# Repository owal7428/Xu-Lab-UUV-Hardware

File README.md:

# Xu-Lab-UUV-Hardware
Hardware design for Xu Lab underwater modular robotic platform project.

Controller board: <br>

Power board: <br>

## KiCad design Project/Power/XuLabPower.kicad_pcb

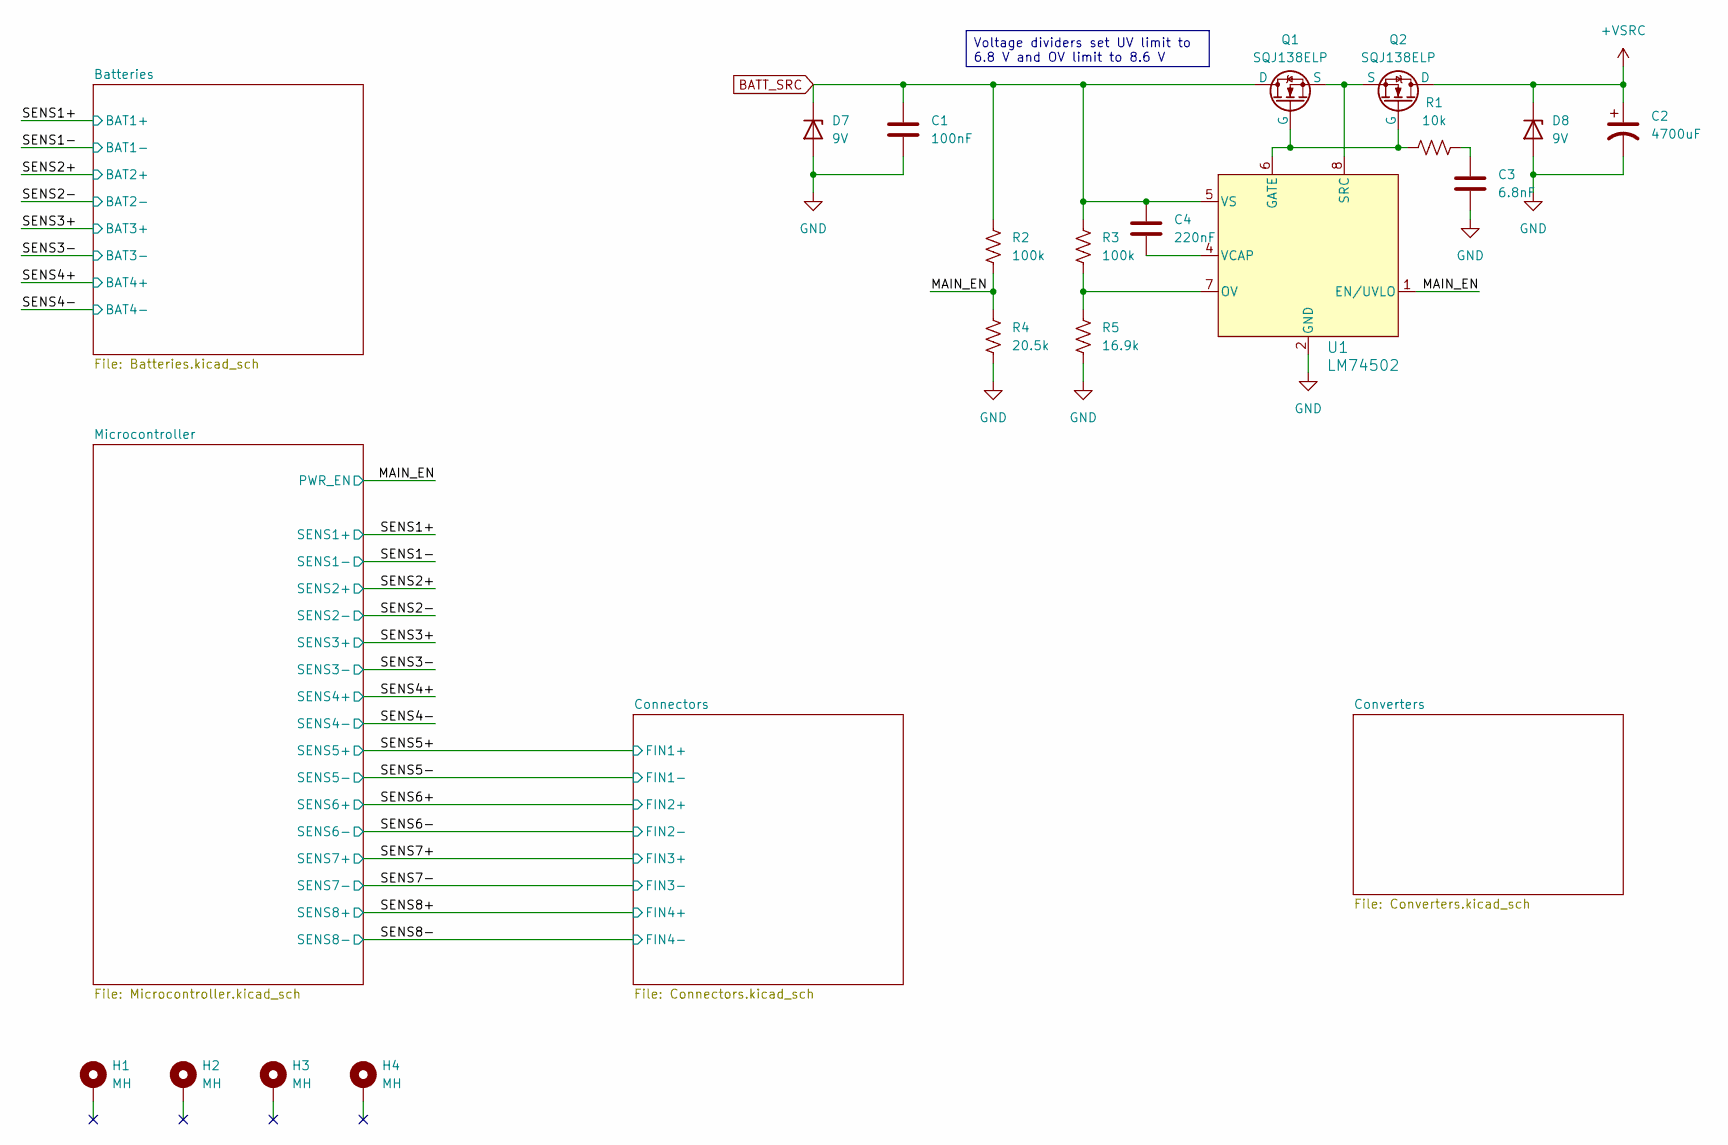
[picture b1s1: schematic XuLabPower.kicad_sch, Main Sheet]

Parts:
C1: 100nF; C_0603_1608Metric
C2: 4700uF; CP_Radial_D12.5mm_P5.00mm
C3: 6.8nF; C_0603_1608Metric
C4: 220nF; C_0603_1608Metric
D7, D8: 9V; D_SMB
H1, H2, H3, H4: MH; MountingHole_2.7mm_M2.5_Pad_Via
Q1, Q2: SQJ138ELP; PowerPAK_SO-8L
R1: 10k; R_0603_1608Metric
R2, R3: 100k; R_0603_1608Metric
R4: 20.5k; R_0603_1608Metric
R5: 16.9k; R_0603_1608Metric
U1: LM74502; TSOT-23-8

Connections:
+VSRC: C2.1, D8.1 (K), Q2.5 (D); also elsewhere on the board
/MAIN_EN: R2.2, R4.1, U1.1 (EN/UVLO); also elsewhere on the board
BATT_SRC: C1.1, C4.1, D7.1 (K), Q1.5 (D), R2.1, R3.1, U1.5 (VS); also elsewhere on the board
GND: C1.2, C2.2, C3.2, D7.2 (A), D8.2 (A), R4.2, R5.2, U1.2 (GND); also elsewhere on the board
unnamed: C3.1, R1.2
unnamed: Q1.4 (G), Q2.4 (G), R1.1, U1.6 (GATE)
unnamed: R3.2, R5.1, U1.7 (OV)
unnamed: Q1.1 (S), Q1.2 (S), Q1.3 (S), Q2.1 (S), Q2.2 (S), Q2.3 (S), U1.8 (SRC)
unnamed: C4.2, U1.4 (VCAP)

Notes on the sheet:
Voltage dividers set UV limit to 6.8 V and OV limit to 8.6 V

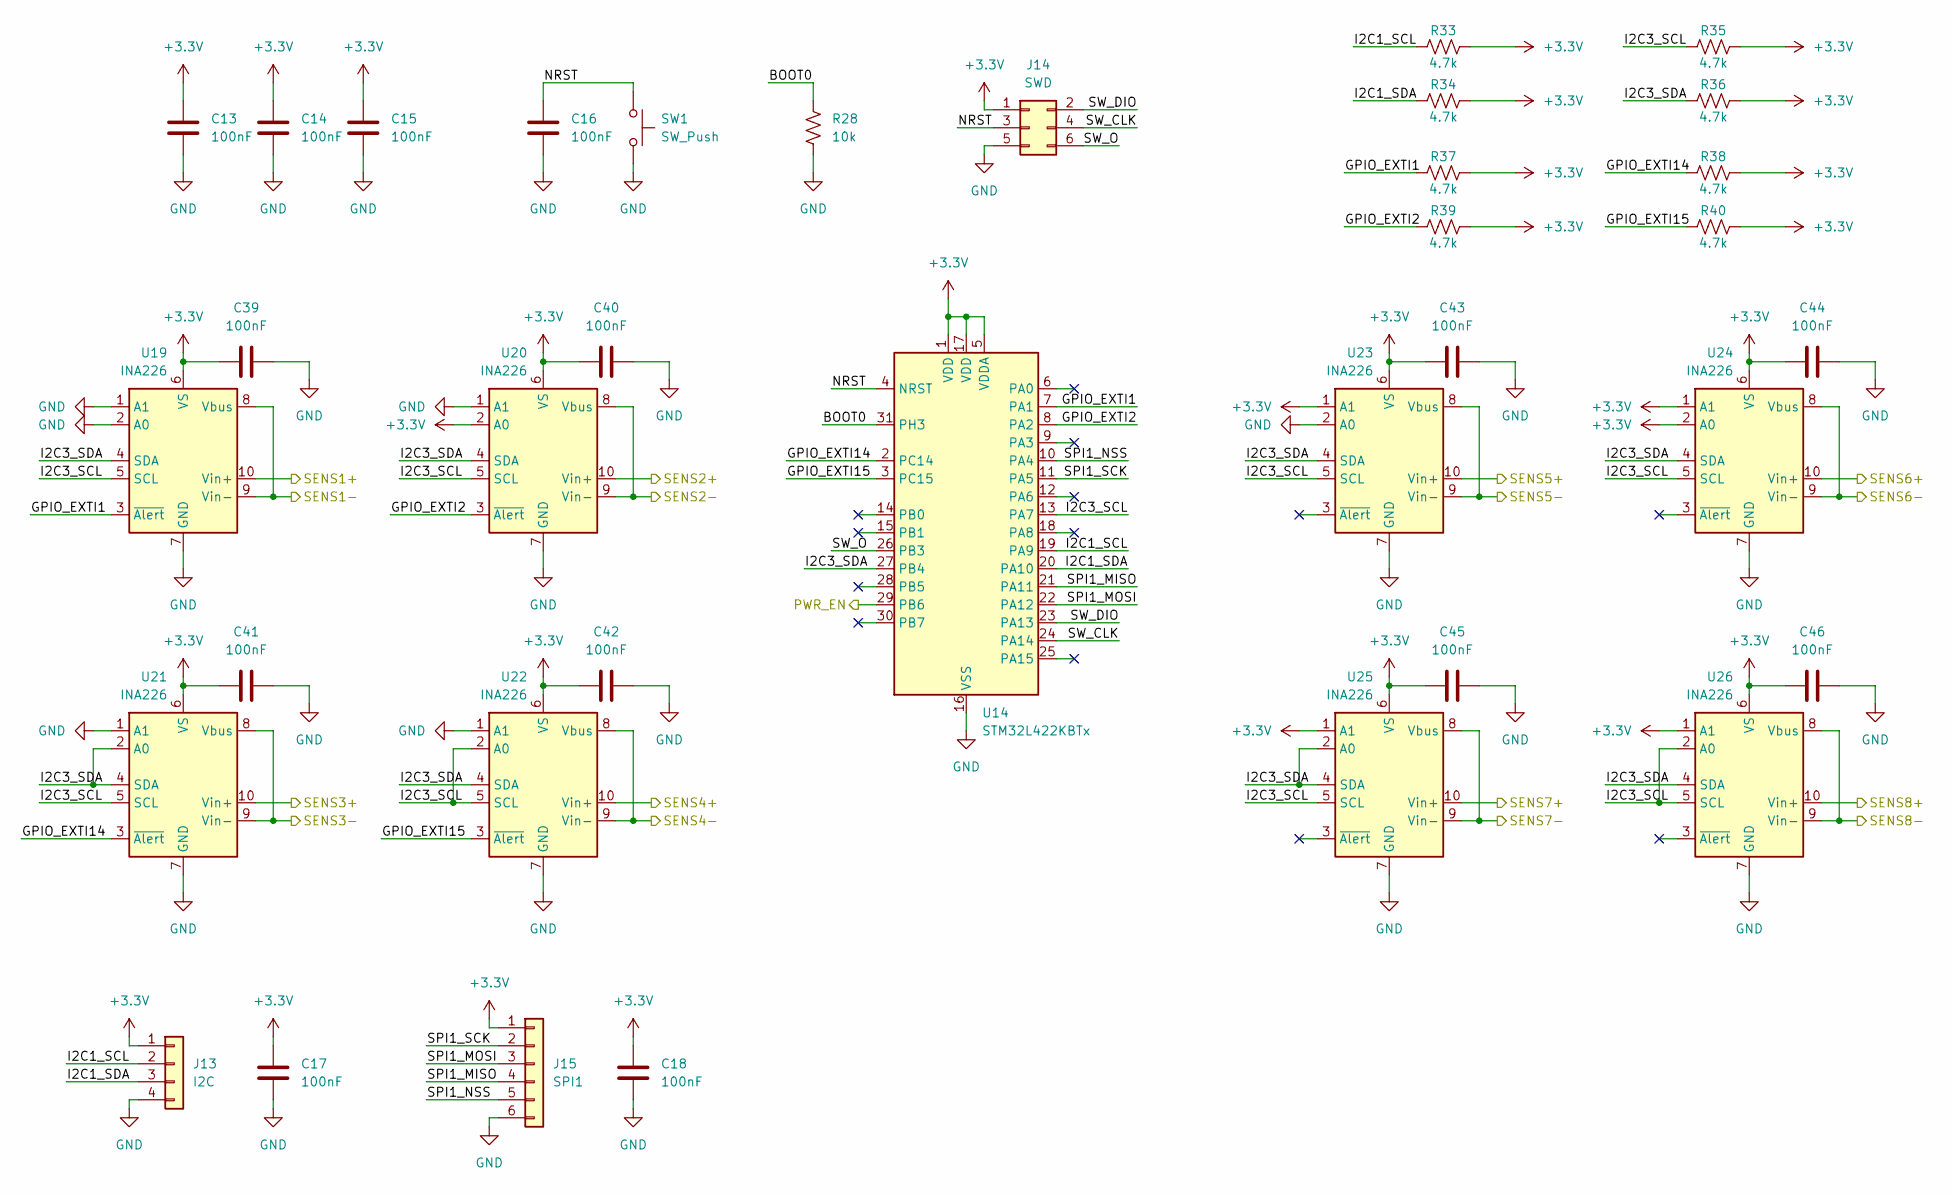
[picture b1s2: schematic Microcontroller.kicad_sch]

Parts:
C13, C14, C15, C16, C17, C18, C39, C40, C41, C42, C43, C44, C45, C46: 100nF; C_0603_1608Metric
J13: I2C; JST_GH_SM04B-GHS-TB_1x04-1MP_P1.25mm_Horizontal
J14: SWD; PinHeader_2x03_P2.54mm_Vertical
J15: SPI1; JST_GH_SM06B-GHS-TB_1x06-1MP_P1.25mm_Horizontal
R28: 10k; R_0603_1608Metric
R33, R34, R35, R36, R37, R38, R39, R40: 4.7k; R_0603_1608Metric
SW1: SW_Push; SW_Push_1P1T_NO_CK_KMR2
U14: STM32L422KBTx; LQFP-32_7x7mm_P0.8mm
U19, U20, U21, U22, U23, U24, U25, U26: INA226; VSSOP-10_3x3mm_P0.5mm

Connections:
+3.3V: C13.1, C14.1, C15.1, C17.1, C18.1, C39.1, C40.1, C41.1, C42.1, C43.1, C44.1, C45.1, C46.1, J13.1, J14.1, J15.1, R33.1, R34.1, R35.1, R36.1, R37.1, R38.1, R39.1, R40.1, U14.1 (VDD), U14.5 (VDDA), U14.17 (VDD), U19.6 (VS), U20.2 (A0), U20.6 (VS), U21.6 (VS), U22.6 (VS), U23.1 (A1), U23.6 (VS), U24.1 (A1), U24.2 (A0), U24.6 (VS), U25.1 (A1), U25.6 (VS), U26.1 (A1), U26.6 (VS); also elsewhere on the board
+VSRC: U23.10 (Vin+), U24.10 (Vin+), U25.10 (Vin+), U26.10 (Vin+); also elsewhere on the board
/MAIN_EN: U14.29 (PB6); also elsewhere on the board
/Microcontroller/BOOT0: R28.2, U14.31 (PH3)
/Microcontroller/GPIO_EXTI1: R37.2, U14.7 (PA1), U19.3 (~Alert)
/Microcontroller/GPIO_EXTI2: R39.2, U14.8 (PA2), U20.3 (~Alert)
/Microcontroller/GPIO_EXTI14: R38.2, U14.2 (PC14), U21.3 (~Alert)
/Microcontroller/GPIO_EXTI15: R40.2, U14.3 (PC15), U22.3 (~Alert)
/Microcontroller/I2C1_SCL: J13.2, R33.2, U14.19 (PA9)
/Microcontroller/I2C1_SDA: J13.3, R34.2, U14.20 (PA10)
/Microcontroller/I2C3_SCL: R35.2, U14.13 (PA7), U19.5 (SCL), U20.5 (SCL), U21.5 (SCL), U22.2 (A0), U22.5 (SCL), U23.5 (SCL), U24.5 (SCL), U25.5 (SCL), U26.2 (A0), U26.5 (SCL)
/Microcontroller/I2C3_SDA: R36.2, U14.27 (PB4), U19.4 (SDA), U20.4 (SDA), U21.2 (A0), U21.4 (SDA), U22.4 (SDA), U23.4 (SDA), U24.4 (SDA), U25.2 (A0), U25.4 (SDA), U26.4 (SDA)
/Microcontroller/LED_OUT1: U14.9 (PA3); also elsewhere on the board
/Microcontroller/LED_OUT2: U14.18 (PA8); also elsewhere on the board
/Microcontroller/NRST: C16.1, J14.3, SW1.1, U14.4 (NRST)
/Microcontroller/SPI1_MISO: J15.4, U14.21 (PA11)
/Microcontroller/SPI1_MOSI: J15.3, U14.22 (PA12)
/Microcontroller/SPI1_NSS: J15.5, U14.10 (PA4)
/Microcontroller/SPI1_SCK: J15.2, U14.11 (PA5)
/Microcontroller/SW_CLK: J14.4, U14.24 (PA14)
/Microcontroller/SW_DIO: J14.2, U14.23 (PA13)
/Microcontroller/SW_O: J14.6, U14.26 (PB3)
/SENS1+: U19.10 (Vin+); also elsewhere on the board
/SENS1-: U19.8 (Vbus), U19.9 (Vin-); also elsewhere on the board
/SENS2+: U20.10 (Vin+); also elsewhere on the board
/SENS2-: U20.8 (Vbus), U20.9 (Vin-); also elsewhere on the board
/SENS3+: U21.10 (Vin+); also elsewhere on the board
/SENS3-: U21.8 (Vbus), U21.9 (Vin-); also elsewhere on the board
/SENS4+: U22.10 (Vin+); also elsewhere on the board
/SENS4-: U22.8 (Vbus), U22.9 (Vin-); also elsewhere on the board
/SENS5-: U23.8 (Vbus), U23.9 (Vin-); also elsewhere on the board
/SENS6-: U24.8 (Vbus), U24.9 (Vin-); also elsewhere on the board
/SENS7-: U25.8 (Vbus), U25.9 (Vin-); also elsewhere on the board
/SENS8-: U26.8 (Vbus), U26.9 (Vin-); also elsewhere on the board
GND: C13.2, C14.2, C15.2, C16.2, C17.2, C18.2, C39.2, C40.2, C41.2, C42.2, C43.2, C44.2, C45.2, C46.2, J13.4, J14.5, J15.6, R28.1, SW1.2, U14.16 (VSS), U14.32 (VSS), U19.1 (A1), U19.2 (A0), U19.7 (GND), U20.1 (A1), U20.7 (GND), U21.1 (A1), U21.7 (GND), U22.1 (A1), U22.7 (GND), U23.2 (A0), U23.7 (GND), U24.7 (GND), U25.7 (GND), U26.7 (GND); also elsewhere on the board

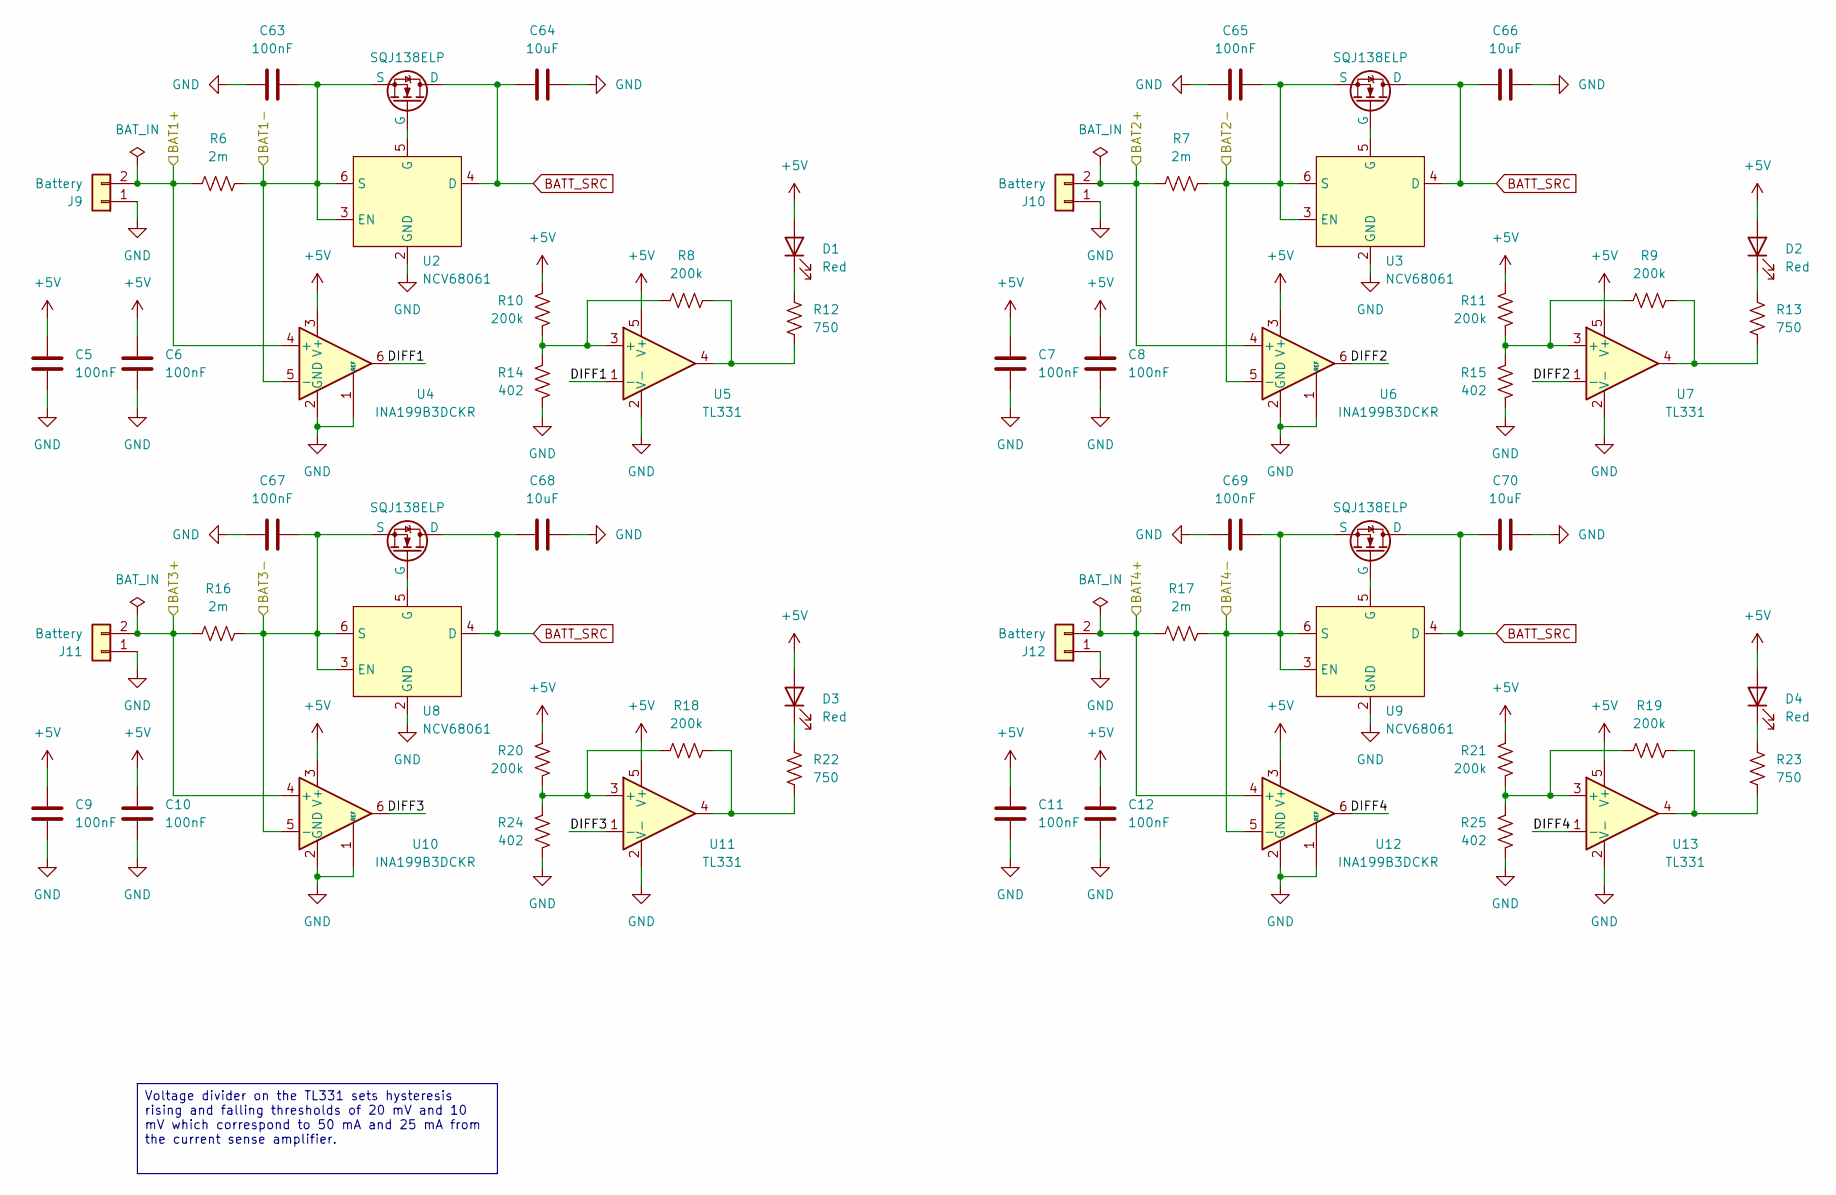
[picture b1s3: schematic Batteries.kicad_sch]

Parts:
C5, C6, C7, C8, C9, C10, C11, C12, C63, C65, C67, C69: 100nF; C_0603_1608Metric
C64, C66, C68, C70: 10uF; C_1206_3216Metric
D1, D2, D3, D4: Red; LED_0603_1608Metric
J9, J10, J11, J12: Battery; AMASS_XT60PW-M_1x02_P7.20mm_Horizontal
Q3, Q4, Q5, Q6: SQJ138ELP; PowerPAK_SO-8L
R6, R7, R16, R17: 2m; R_2512_6332Metric
R8, R9, R10, R11, R18, R19, R20, R21: 200k; R_0603_1608Metric
R12, R13, R22, R23: 750; R_0603_1608Metric
R14, R15, R24, R25: 402; R_0603_1608Metric
U2, U3, U8, U9: NCV68061; TSOT-23-6
U4, U6, U10, U12: INA199B3DCKR; SOT-363_SC-70-6
U5, U7, U11, U13: TL331; SOT-23-5

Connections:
+5V: C5.1, C6.1, C7.1, C8.1, C9.1, C10.1, C11.1, C12.1, D1.2 (A), D2.2 (A), D3.2 (A), D4.2 (A), R10.1, R11.1, R20.1, R21.1, U4.3 (V+), U5.5 (V+), U6.3 (V+), U7.5 (V+), U10.3 (V+), U11.5 (V+), U12.3 (V+), U13.5 (V+); also elsewhere on the board
/Batteries/DIFF1: U4.6, U5.1 (-)
/Batteries/DIFF2: U6.6, U7.1 (-)
/Batteries/DIFF3: U10.6, U11.1 (-)
/Batteries/DIFF4: U12.6, U13.1 (-)
/SENS1+: J9.2, R6.1, U4.4 (+); also elsewhere on the board
/SENS1-: C63.2, Q3.1 (S), Q3.2 (S), Q3.3 (S), R6.2, U2.3 (EN), U2.6 (S), U4.5 (-); also elsewhere on the board
/SENS2+: J10.2, R7.1, U6.4 (+); also elsewhere on the board
/SENS2-: C65.2, Q4.1 (S), Q4.2 (S), Q4.3 (S), R7.2, U3.3 (EN), U3.6 (S), U6.5 (-); also elsewhere on the board
/SENS3+: J11.2, R16.1, U10.4 (+); also elsewhere on the board
/SENS3-: C67.2, Q5.1 (S), Q5.2 (S), Q5.3 (S), R16.2, U8.3 (EN), U8.6 (S), U10.5 (-); also elsewhere on the board
/SENS4+: J12.2, R17.1, U12.4 (+); also elsewhere on the board
/SENS4-: C69.2, Q6.1 (S), Q6.2 (S), Q6.3 (S), R17.2, U9.3 (EN), U9.6 (S), U12.5 (-); also elsewhere on the board
BATT_SRC: C64.1, C66.1, C68.1, C70.1, Q3.5 (D), Q4.5 (D), Q5.5 (D), Q6.5 (D), U2.4 (D), U3.4 (D), U8.4 (D), U9.4 (D); also elsewhere on the board
GND: C5.2, C6.2, C7.2, C8.2, C9.2, C10.2, C11.2, C12.2, C63.1, C64.2, C65.1, C66.2, C67.1, C68.2, C69.1, C70.2, J9.1, J10.1, J11.1, J12.1, R14.2, R15.2, R24.2, R25.2, U2.1, U2.2 (GND), U3.1, U3.2 (GND), U4.1 (REF), U4.2 (GND), U5.2 (V-), U6.1 (REF), U6.2 (GND), U7.2 (V-), U8.1, U8.2 (GND), U9.1, U9.2 (GND), U10.1 (REF), U10.2 (GND), U11.2 (V-), U12.1 (REF), U12.2 (GND), U13.2 (V-); also elsewhere on the board
unnamed: D1.1 (K), R12.2
unnamed: D2.1 (K), R13.2
unnamed: D3.1 (K), R22.2
unnamed: D4.1 (K), R23.2
unnamed: Q3.4 (G), U2.5 (G)
unnamed: Q4.4 (G), U3.5 (G)
unnamed: Q5.4 (G), U8.5 (G)
unnamed: Q6.4 (G), U9.5 (G)
unnamed: R8.2, R12.1, U5.4
unnamed: R9.2, R13.1, U7.4
unnamed: R18.2, R22.1, U11.4
unnamed: R19.2, R23.1, U13.4
unnamed: R8.1, R10.2, R14.1, U5.3 (+)
unnamed: R9.1, R11.2, R15.1, U7.3 (+)
unnamed: R18.1, R20.2, R24.1, U11.3 (+)
unnamed: R19.1, R21.2, R25.1, U13.3 (+)

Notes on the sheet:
Voltage divider on the TL331 sets hysteresis rising and falling thresholds of 20 mV and 10 mV which correspond to 50 mA and 25 mA from the current sense amplifier.

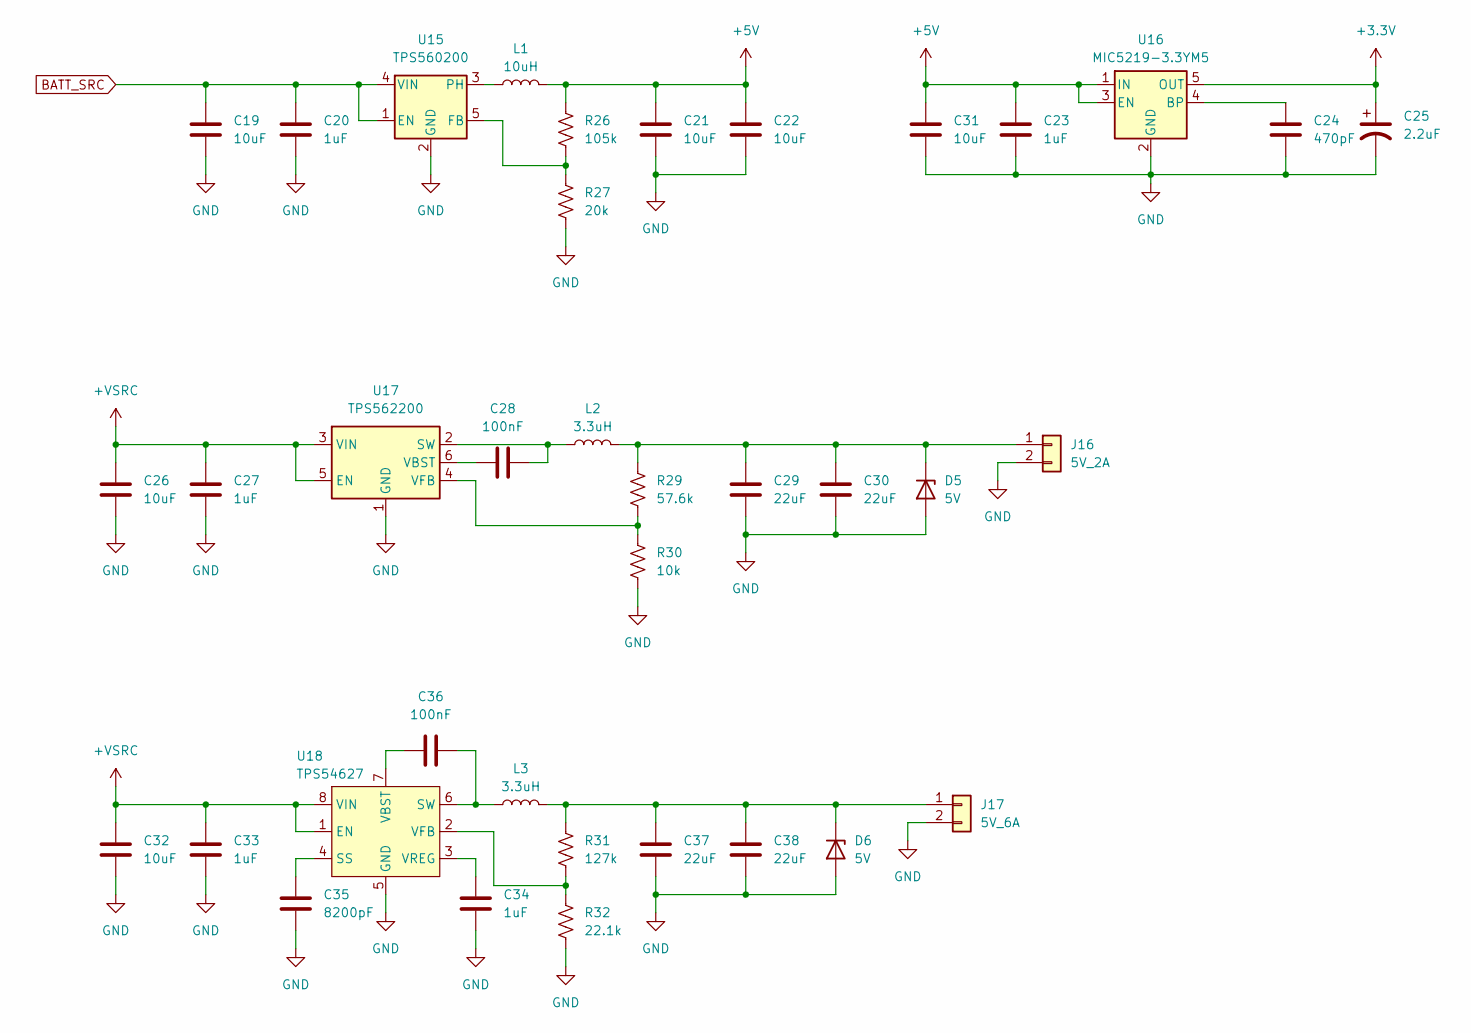
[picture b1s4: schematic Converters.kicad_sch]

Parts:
C19, C21, C22, C26, C31, C32: 10uF; C_1206_3216Metric
C20, C23, C27, C33, C34: 1uF; C_0603_1608Metric
C24: 470pF; C_0603_1608Metric
C25: 2.2uF; CP_EIA-3216-18_Kemet-A
C28, C36: 100nF; C_0603_1608Metric
C29, C30, C37, C38: 22uF; C_1206_3216Metric
C35: 8200pF; C_0603_1608Metric
D5, D6: 5V; D_MicroSMP_KA
J16: 5V_2A; JST_XH_S2B-XH-A_1x02_P2.50mm_Horizontal
J17: 5V_6A; JST_VH_S2P-VH_1x02_P3.96mm_Horizontal
L1: 10uH; L_1210_3225Metric
L2, L3: 3.3uH; L_APV_APH0630
R26: 105k; R_0603_1608Metric
R27: 20k; R_0603_1608Metric
R29: 57.6k; R_0603_1608Metric
R30: 10k; R_0603_1608Metric
R31: 127k; R_0603_1608Metric
R32: 22.1k; R_0603_1608Metric
U15: TPS560200; SOT-23-5
U16: MIC5219-3.3YM5; SOT-23-5
U17: TPS562200; SOT-23-6
U18: TPS54627; SOIC-8-1EP_3.9x4.9mm_P1.27mm_EP2.95x4.9mm_Mask2.71x3.4mm_Th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

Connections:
+3.3V: C25.1, U16.5 (OUT); also elsewhere on the board
+5V: C21.1, C22.1, C23.1, C31.1, L1.2, R26.1, U16.1 (IN), U16.3 (EN); also elsewhere on the board
+VSRC: C26.1, C27.1, C32.1, C33.1, U17.3 (VIN), U17.5 (EN), U18.1 (EN), U18.8 (VIN); also elsewhere on the board
BATT_SRC: C19.1, C20.1, U15.1 (EN), U15.4 (VIN); also elsewhere on the board
GND: C19.2, C20.2, C21.2, C22.2, C23.2, C24.2, C25.2, C26.2, C27.2, C29.2, C30.2, C31.2, C32.2, C33.2, C34.2, C35.2, C37.2, C38.2, D5.2 (A), D6.2 (A), J16.2, J17.2, R27.2, R30.1, R32.1, U15.2 (GND), U16.2 (GND), U17.1 (GND), U18.5 (GND), U18.9 (GND); also elsewhere on the board
unnamed: C29.1, C30.1, D5.1 (K), J16.1, L2.2, R29.1
unnamed: C37.1, C38.1, D6.1 (K), J17.1, L3.2, R31.1
unnamed: R26.2, R27.1, U15.5 (FB)
unnamed: L1.1, U15.3 (PH)
unnamed: C24.1, U16.4 (BP)
unnamed: C28.2, L2.1, U17.2 (SW)
unnamed: C28.1, U17.6 (VBST)
unnamed: R29.2, R30.2, U17.4 (VFB)
unnamed: C35.1, U18.4 (SS)
unnamed: C36.2, L3.1, U18.6 (SW)
unnamed: C36.1, U18.7 (VBST)
unnamed: R31.2, R32.2, U18.2 (VFB)
unnamed: C34.1, U18.3 (VREG)

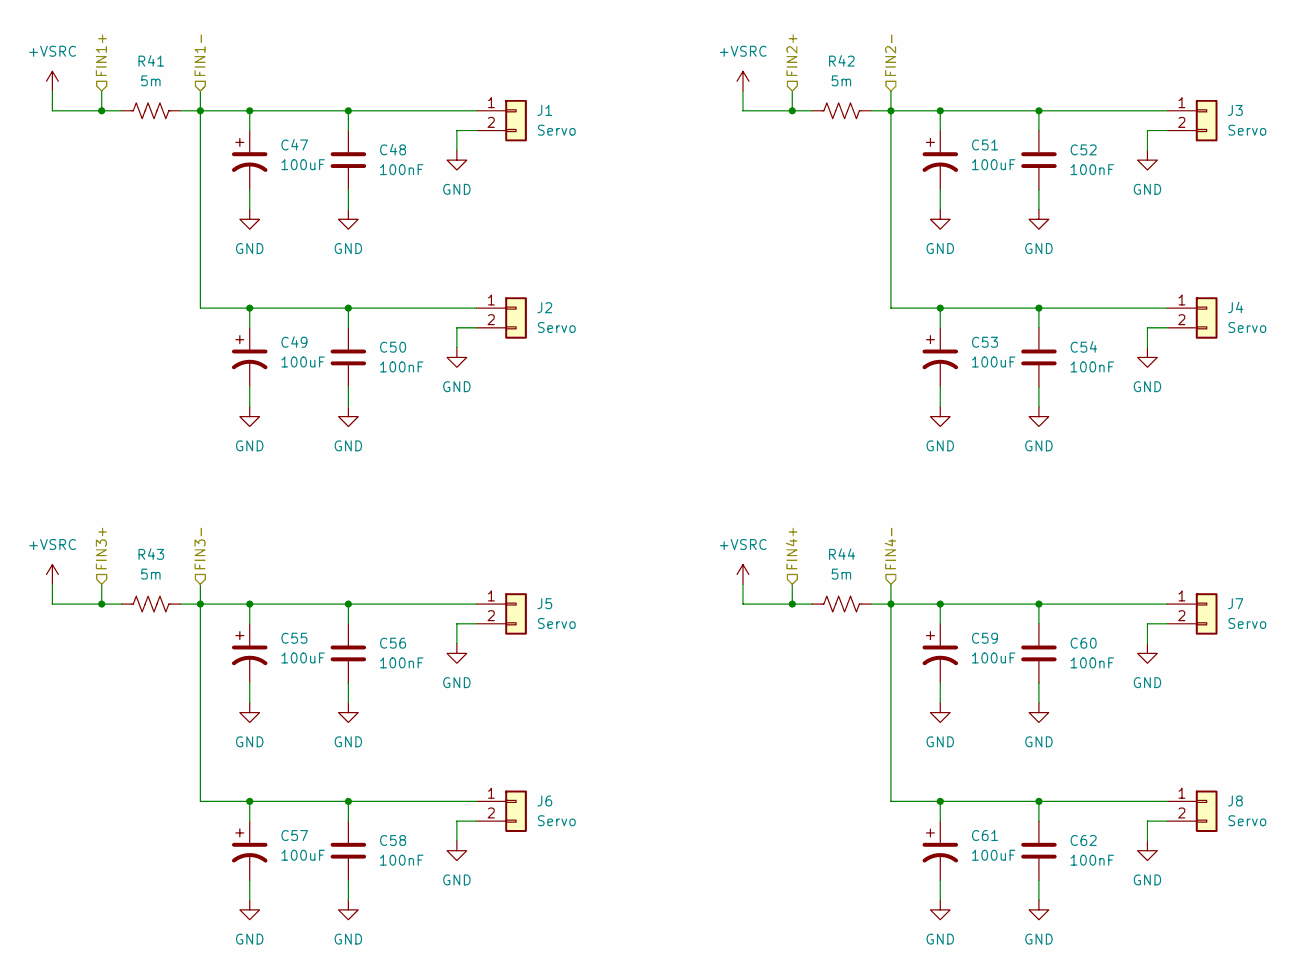
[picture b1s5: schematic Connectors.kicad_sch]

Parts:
C47, C49, C51, C53, C55, C57, C59, C61: 100uF; CP_Radial_D6.3mm_P2.50mm
C48, C50, C52, C54, C56, C58, C60, C62: 100nF; C_0603_1608Metric
J1, J2, J3, J4, J5, J6, J7, J8: Servo; JST_VH_B2P-VH_1x02_P3.96mm_Vertical
R41, R42, R43, R44: 5m; R_0805_2012Metric

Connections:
+VSRC: R41.1, R42.1, R43.1, R44.1; also elsewhere on the board
/SENS5-: C47.1, C48.1, C49.1, C50.1, J1.1, J2.1, R41.2; also elsewhere on the board
/SENS6-: C51.1, C52.1, C53.1, C54.1, J3.1, J4.1, R42.2; also elsewhere on the board
/SENS7-: C55.1, C56.1, C57.1, C58.1, J5.1, J6.1, R43.2; also elsewhere on the board
/SENS8-: C59.1, C60.1, C61.1, C62.1, J7.1, J8.1, R44.2; also elsewhere on the board
GND: C47.2, C48.2, C49.2, C50.2, C51.2, C52.2, C53.2, C54.2, C55.2, C56.2, C57.2, C58.2, C59.2, C60.2, C61.2, C62.2, J1.2, J2.2, J3.2, J4.2, J5.2, J6.2, J7.2, J8.2; also elsewhere on the board

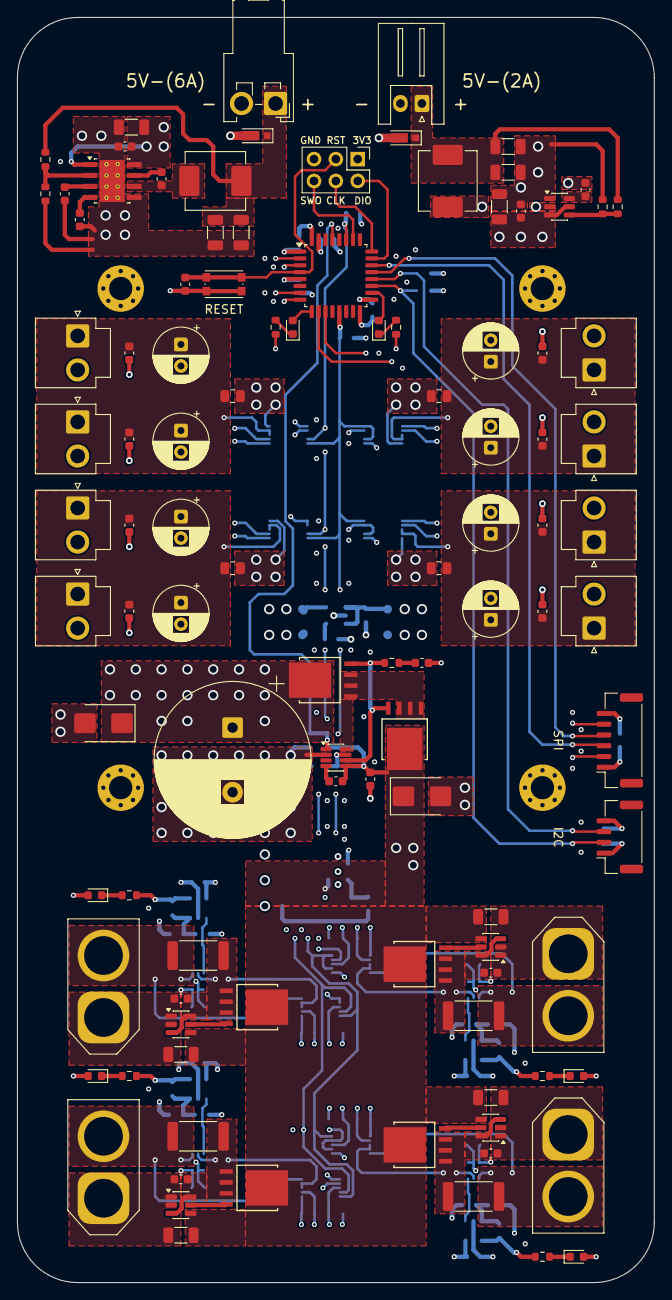
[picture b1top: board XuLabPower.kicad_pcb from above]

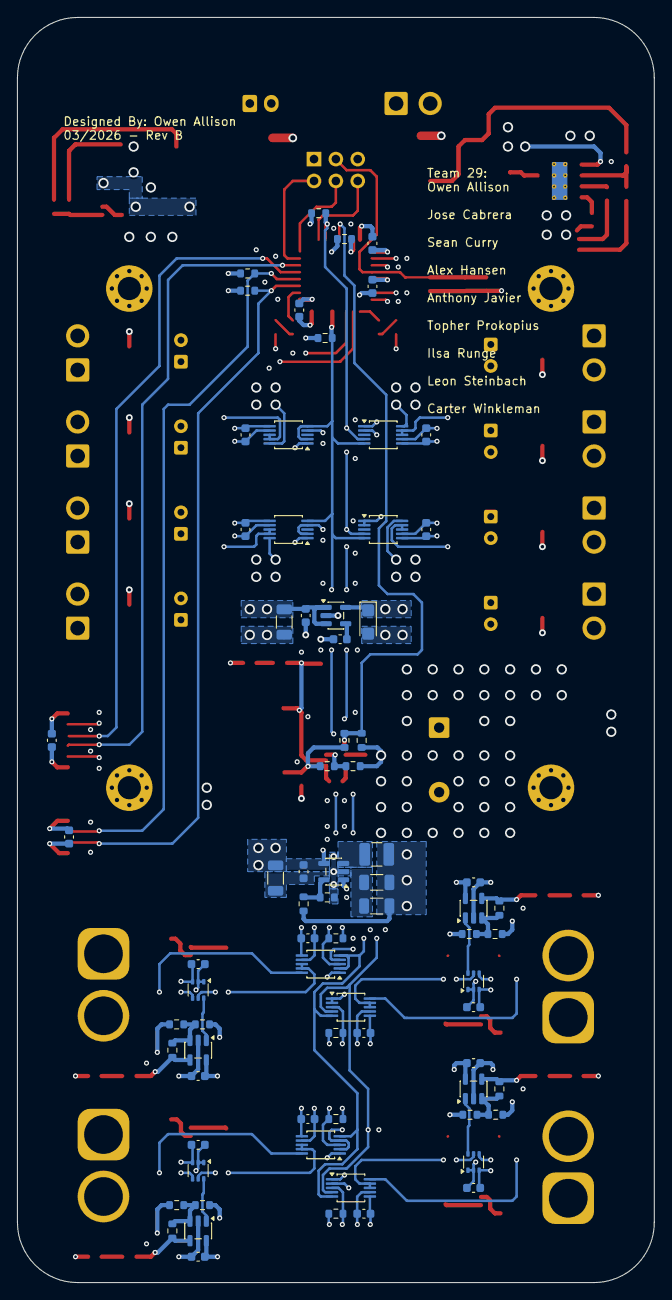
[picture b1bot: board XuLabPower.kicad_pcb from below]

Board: 8 copper layers, 74.0 x 147.0 mm, 183 parts (75 on the bottom side), 77 nets.

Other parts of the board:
D9: Amber; LED_0603_1608Metric
D10: Green; LED_0603_1608Metric
R45, R46: 330; R_0603_1608Metric

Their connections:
/Microcontroller/LED_OUT1: D9.2 (A); also elsewhere on the board
/Microcontroller/LED_OUT2: D10.2 (A); also elsewhere on the board
GND: R45.2, R46.2; also elsewhere on the board
unnamed: D9.1 (K), R45.1
unnamed: D10.1 (K), R46.1
